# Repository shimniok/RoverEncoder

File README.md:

Various incarnations of schmitt-trigger (optical) wheel encoder adapters.

* 555/ - using a 555 timer
* 7414/ - using a 74*14 Hex Inverter Schmitt Trigger IC
* 74LVC/ - using a single (LVC) 74*14 Hex Inverter Schmitt Trigger IC
* QRE1113_schmitt/ - attempt at a QRE1113 breakout incorporating Schmitt trigger
* RoverEncoder/ - Basic QRE1113 breakout 
* WheelEncoderAdapter/ - Schmitt trigger implemented with comparator

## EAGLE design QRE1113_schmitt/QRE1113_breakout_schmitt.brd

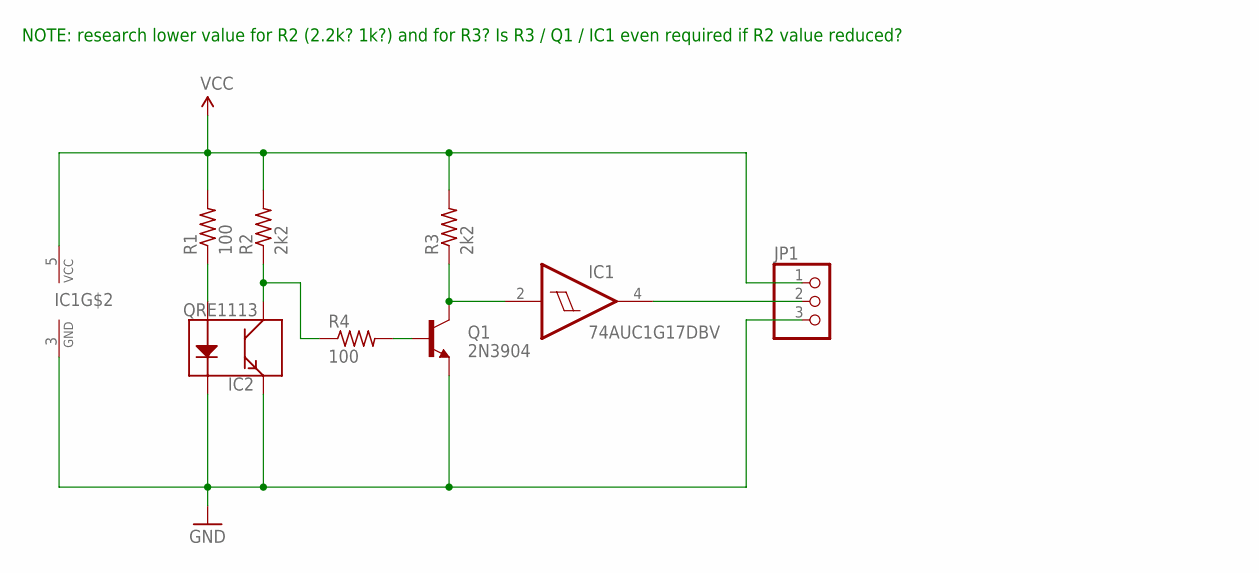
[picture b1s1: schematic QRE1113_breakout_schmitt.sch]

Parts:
IC1: 74AUC1G17DBV; SOT23-5
IC2: QRE1113
JP1: PINHD-1X03_2.54-S; 1X03-S
Q1: 2N3904; SOT-23
R1, R4: 100; R0603
R2, R3: 2k2; R0603

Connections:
GND: IC1.3 (GND), IC2.2 (K), IC2.4 (E), JP1.3, Q1.2 (E)
unnamed: IC2.3 (C), R2.1, R4.1
unnamed: IC2.1 (A), R1.1
unnamed: IC1.2 (I), Q1.1 (C), R3.1
unnamed: Q1.3 (B), R4.2
SIG: IC1.4 (O), JP1.2
VCC: IC1.5 (VCC), JP1.1, R1.2, R2.2, R3.2

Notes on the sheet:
NOTE: research lower value for R2 (2.2k? 1k?) and for R3? Is R3 / Q1 / IC1 even required if R2 value reduced?

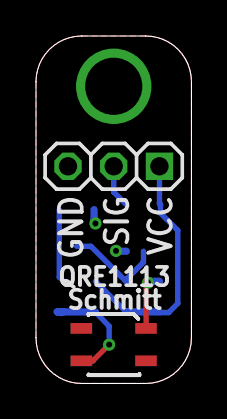
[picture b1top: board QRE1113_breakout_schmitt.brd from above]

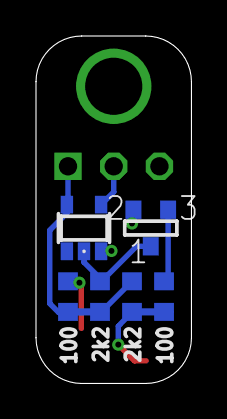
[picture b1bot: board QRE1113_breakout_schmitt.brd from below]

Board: 2 copper layers, 8.6 x 19.3 mm, 8 parts (6 on the bottom side), 7 nets.

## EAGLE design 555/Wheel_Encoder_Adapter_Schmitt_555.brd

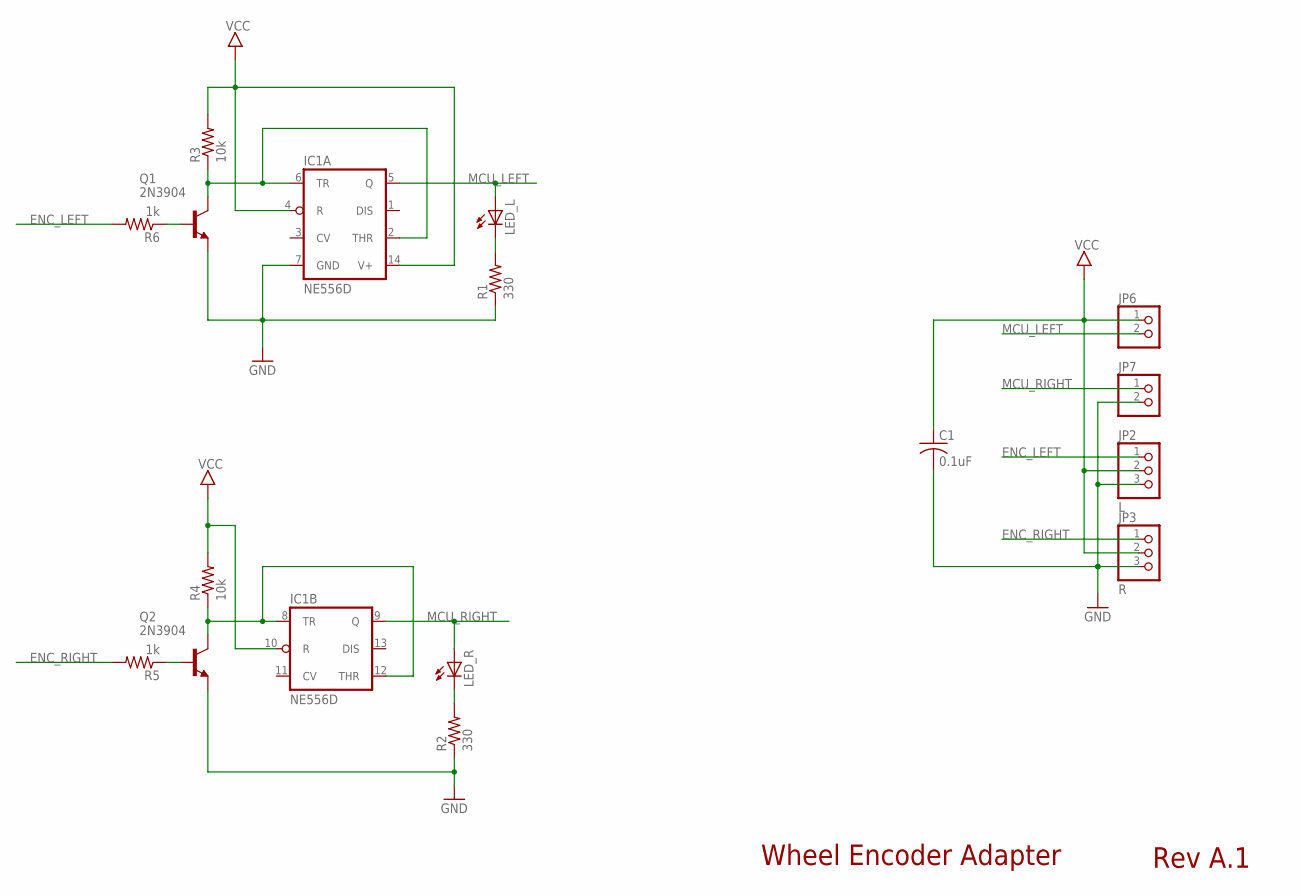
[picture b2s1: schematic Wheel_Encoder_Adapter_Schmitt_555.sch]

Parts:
C1: 0.1uF; C0603
IC1: NE556D; SO14
JP2: L; 1X03-S
JP3: R; 1X03-S
JP6, JP7: PINHD-1X02_2.54-S; 1X02-S
LED_L: LEDCHIPLED_0805; CHIPLED_0805
LED_R: LEDCHIPLED_0805; CHIPLED_0805
Q1, Q2: 2N3904; SOT-23
R1, R2: 330; R0603
R3, R4: 10k; R0603
R5, R6: 1k; R0603

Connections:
ENC_LEFT: JP2.1, R6.2
ENC_RIGHT: JP3.1, R5.2
GND: C1.2, IC1.7 (GND), JP2.3, JP3.3, JP7.2, Q1.2 (E), Q2.2 (E), R1.1, R2.1
MCU_LEFT: IC1.5 (Q), JP6.2, LED_L.A
MCU_RIGHT: IC1.9 (Q), JP7.1, LED_R.A
unnamed: LED_L.C, R1.2
unnamed: LED_R.C, R2.2
unnamed: Q2.3 (B), R5.1
unnamed: Q1.3 (B), R6.1
unnamed: IC1.8 (TR), IC1.12 (THR), Q2.1 (C), R4.1
unnamed: IC1.2 (THR), IC1.6 (TR), Q1.1 (C), R3.1
VCC: C1.1, IC1.4 (R), IC1.10 (R), IC1.14 (V+), JP2.2, JP3.2, JP6.1, R3.2, R4.2

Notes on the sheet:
Wheel Encoder Adapter
Rev A.1

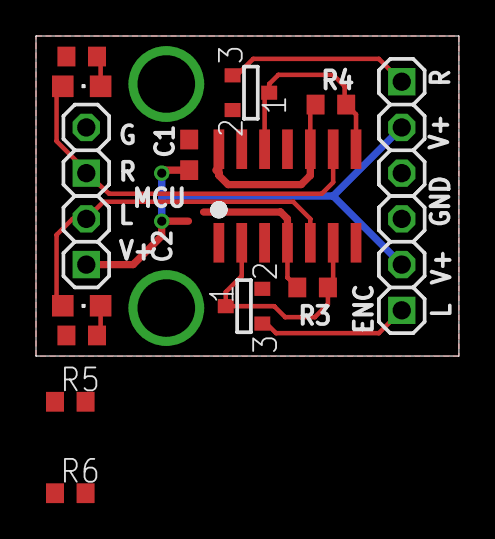
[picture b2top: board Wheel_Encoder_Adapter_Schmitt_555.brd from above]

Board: 2 copper layers, 23.5 x 17.8 mm, 16 parts (0 on the bottom side), 12 nets.

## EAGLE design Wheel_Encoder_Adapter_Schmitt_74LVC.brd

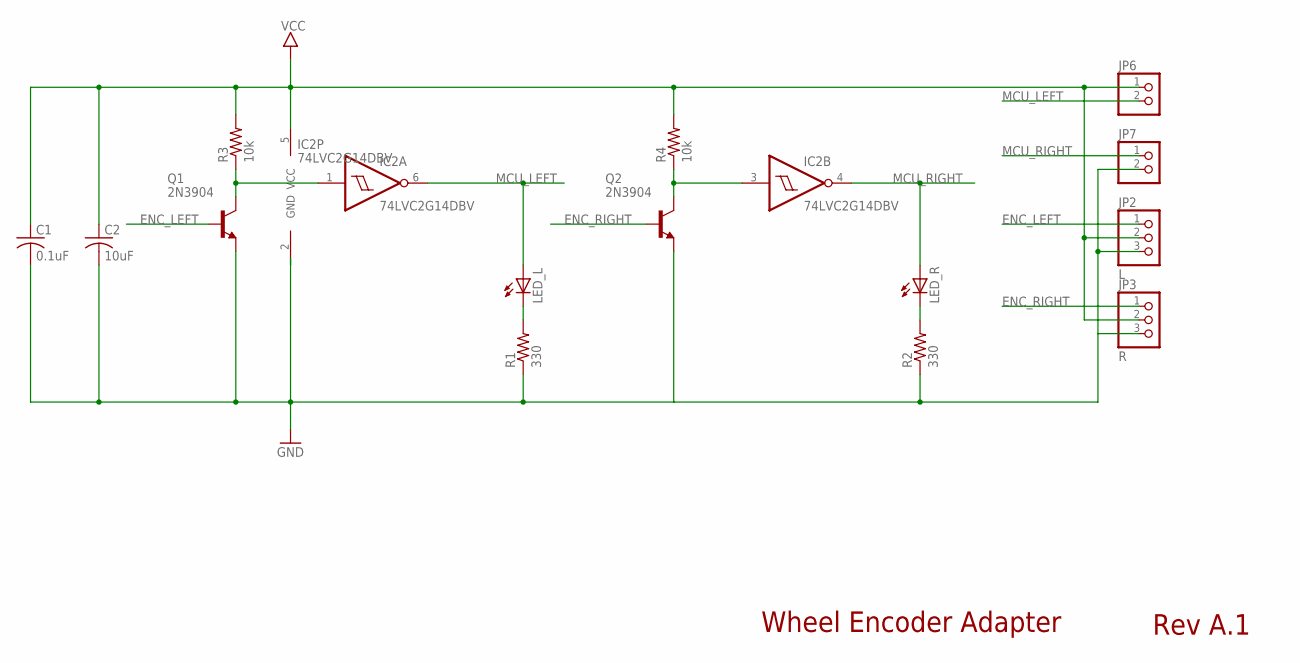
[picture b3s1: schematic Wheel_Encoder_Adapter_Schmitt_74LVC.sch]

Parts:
C1: 0.1uF; C0603
C2: 10uF; C0603
IC2: 74LVC2G14DBV; SOT23-6
JP2: L; 1X03-S
JP3: R; 1X03-S
JP6, JP7: PINHD-1X02_2.54-S; 1X02-S
LED_L: LEDCHIPLED_0805; CHIPLED_0805
LED_R: LEDCHIPLED_0805; CHIPLED_0805
Q1, Q2: 2N3904; SOT-23
R1, R2: 330; R0603
R3, R4: 10k; R0603

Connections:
ENC_LEFT: JP2.1, Q1.3 (B)
ENC_RIGHT: JP3.1, Q2.3 (B)
GND: C1.2, C2.2, IC2.2 (GND), JP2.3, JP3.3, JP7.2, Q1.2 (E), Q2.2 (E), R1.1, R2.1
MCU_LEFT: IC2.6 (O), JP6.2, LED_L.A
MCU_RIGHT: IC2.4 (O), JP7.1, LED_R.A
unnamed: LED_L.C, R1.2
unnamed: LED_R.C, R2.2
unnamed: IC2.3 (I), Q2.1 (C), R4.1
unnamed: IC2.1 (I), Q1.1 (C), R3.1
VCC: C1.1, C2.1, IC2.5 (VCC), JP2.2, JP3.2, JP6.1, R3.2, R4.2

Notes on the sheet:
Wheel Encoder Adapter
Rev A.1

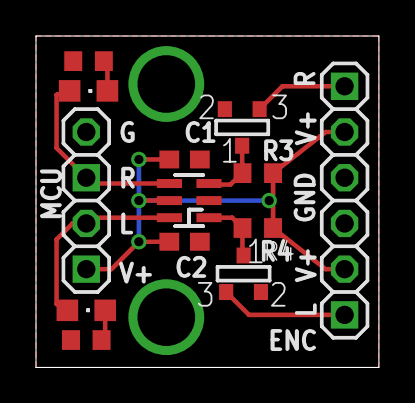
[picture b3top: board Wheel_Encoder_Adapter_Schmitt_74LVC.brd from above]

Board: 2 copper layers, 19.1 x 18.4 mm, 15 parts (0 on the bottom side), 10 nets.

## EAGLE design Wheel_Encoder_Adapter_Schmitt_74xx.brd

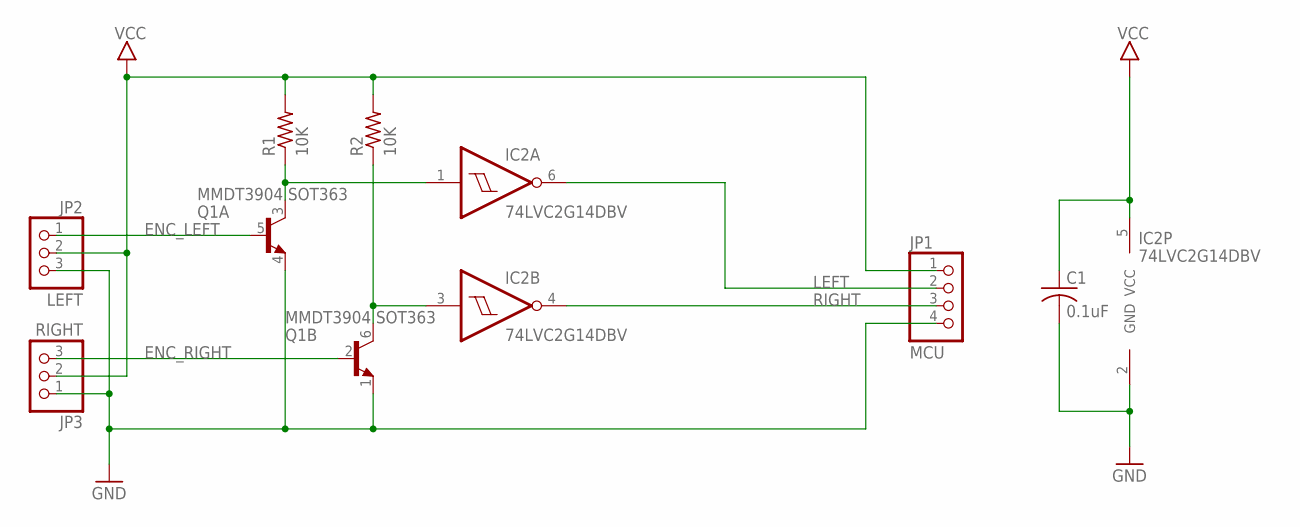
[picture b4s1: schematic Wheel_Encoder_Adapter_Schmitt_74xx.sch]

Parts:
C1: 0.1uF; C0603
IC2: 74LVC2G14DBV; SOT23-6
JP1: MCU; 1X04-S
JP2: LEFT; 1X03-S
JP3: RIGHT; 1X03-S
Q1: MMDT3904 SOT363; SOT363
R1, R2: 10K; R0603

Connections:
ENC_LEFT: JP2.1, Q1.5 (B)
ENC_RIGHT: JP3.3, Q1.2 (B)
GND: C1.2, IC2.2 (GND), JP1.4, JP2.3, JP3.1, Q1.1 (E), Q1.4 (E)
LEFT: IC2.6 (O), JP1.2
unnamed: IC2.1 (I), Q1.3 (C), R1.1
unnamed: IC2.3 (I), Q1.6 (C), R2.1
RIGHT: IC2.4 (O), JP1.3
VCC: C1.1, IC2.5 (VCC), JP1.1, JP2.2, JP3.2, R1.2, R2.2

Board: 2 copper layers, 8 parts (5 on the bottom side), 8 nets, no tracks yet.

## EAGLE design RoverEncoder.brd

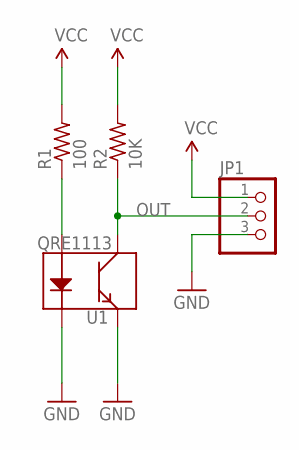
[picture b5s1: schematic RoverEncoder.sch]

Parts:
JP1: PINHD-1X03_2.54-S; 1X03-S
R1: 100; R0603
R2: 10K; R0603
U1: QRE1113

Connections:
GND: JP1.3, U1.2 (K), U1.4 (E)
unnamed: R1.1, U1.1 (A)
OUT: JP1.2, R2.1, U1.3 (C)
VCC: JP1.1, R1.2, R2.2

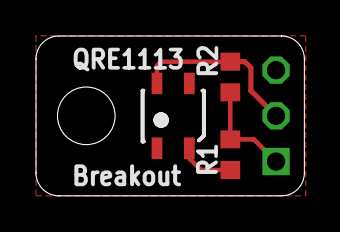
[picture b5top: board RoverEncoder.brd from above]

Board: 2 copper layers, 14.9 x 8.9 mm, 4 parts (1 on the bottom side), 4 nets.

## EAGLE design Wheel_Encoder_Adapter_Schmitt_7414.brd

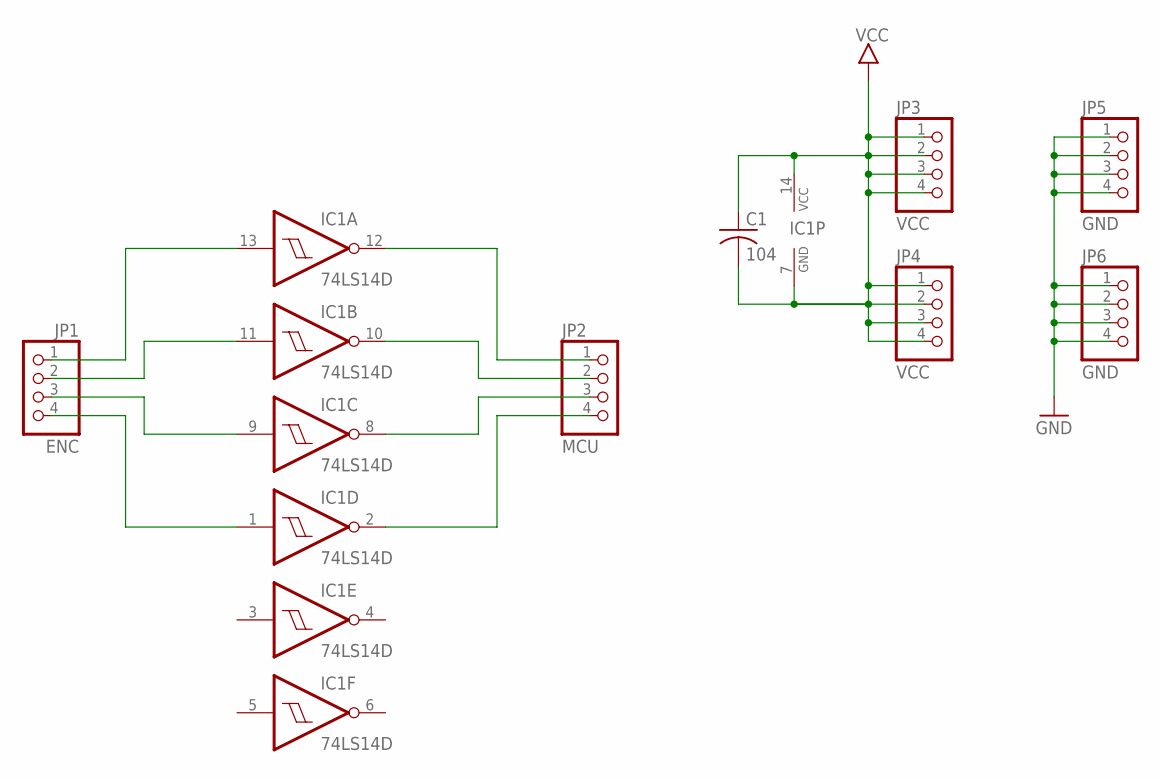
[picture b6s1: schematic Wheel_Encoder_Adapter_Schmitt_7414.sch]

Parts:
C1: 104; C0603
IC1: 74LS14D; SO14
JP1: ENC; 1X04-S
JP2: MCU; 1X04-S
JP3, JP4: VCC; 1X04-S
JP5, JP6: GND; 1X04-S

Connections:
GND: JP5.1, JP5.2, JP5.3, JP5.4, JP6.1, JP6.2, JP6.3, JP6.4
unnamed: IC1.13 (I), JP1.1
unnamed: IC1.1 (I), JP1.4
unnamed: IC1.12 (O), JP2.1
unnamed: IC1.2 (O), JP2.4
unnamed: IC1.8 (O), JP2.3
unnamed: IC1.10 (O), JP2.2
unnamed: IC1.11 (I), JP1.2
unnamed: IC1.9 (I), JP1.3
VCC: C1.1, C1.2, IC1.7 (GND), IC1.14 (VCC), JP3.1, JP3.2, JP3.3, JP3.4, JP4.1, JP4.2, JP4.3, JP4.4

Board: 2 copper layers, 8 parts (0 on the bottom side), 10 nets, no tracks yet.

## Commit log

2015-05-08 Initial release
2015-05-08 Added Eagle description file
2015-05-08 moved versions into separate subdirectories, added README
2015-05-08 Moved DESCRIPTION to QRE1113 directory
2015-05-08 Removed unfinished duplicate 74xx variant
2015-05-09 Moved variants into separate subdirectories
2015-05-10 Initial version of qre1113 breakout with onboard schmitt

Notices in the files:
parts and their libraries:
SparkFun: Licensing: CC v3.0 Share-Alike You are welcome to use this library for commercial purposes.
